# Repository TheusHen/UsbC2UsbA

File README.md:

# USB-C to USB-A Adapter
My first PCB, warming up and learning to Hack Club Highway 2026!

## PCB:

*Layers: 2*

*Dimensions: 30.6 x 63.2 mm*

### License: [GPLv3](https://www.gnu.org/licenses/gpl-3.0.html)

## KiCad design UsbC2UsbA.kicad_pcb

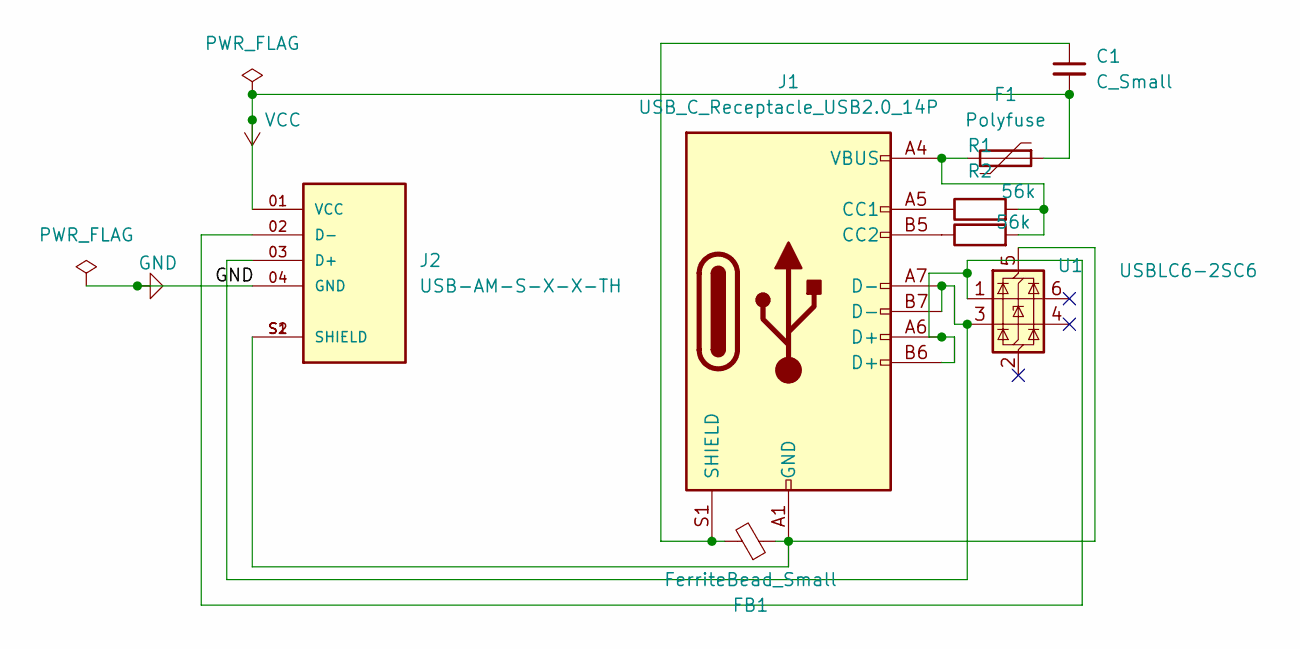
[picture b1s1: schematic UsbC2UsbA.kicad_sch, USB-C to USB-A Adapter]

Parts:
C1: C_Small; C_0603_1608Metric
F1: Polyfuse; Fuse_Schurter_UMT250
FB1: FerriteBead_Small; LairdTech_28C0236-0JW-10
J1: USB_C_Receptacle_USB2.0_14P; USB_C_Receptacle_HRO_TYPE-C-31-M-12
J2: USB-AM-S-X-X-TH; SAMTEC_USB-AM-S-X-X-TH; PARTREV U
R1, R2: 56k; R_0603_1608Metric
U1: USBLC6-2SC6; SOT-23-6

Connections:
GND: J2.04 (GND)
unnamed: F1.2, J1.A4 (VBUS), J1.A9 (VBUS), J1.B4 (VBUS), J1.B9 (VBUS), R1.2, R2.2
unnamed: J1.A5 (CC1), R1.1
unnamed: J1.B5 (CC2), R2.1
unnamed: C1.1, FB1.2, J1.S1 (SHIELD)
unnamed: J1.A7 (D-), J1.B7 (D-), J2.03 (D+), U1.3 (I/O2)
unnamed: J1.A6 (D+), J1.B6 (D+), J2.02 (D-), U1.1 (I/O1)
unnamed: FB1.1, J1.A1 (GND), J1.A12 (GND), J1.B1 (GND), J1.B12 (GND), J2.S1 (SHIELD), J2.S2 (SHIELD), U1.5 (VBUS)
VCC: C1.2, F1.1, J2.01 (VCC)

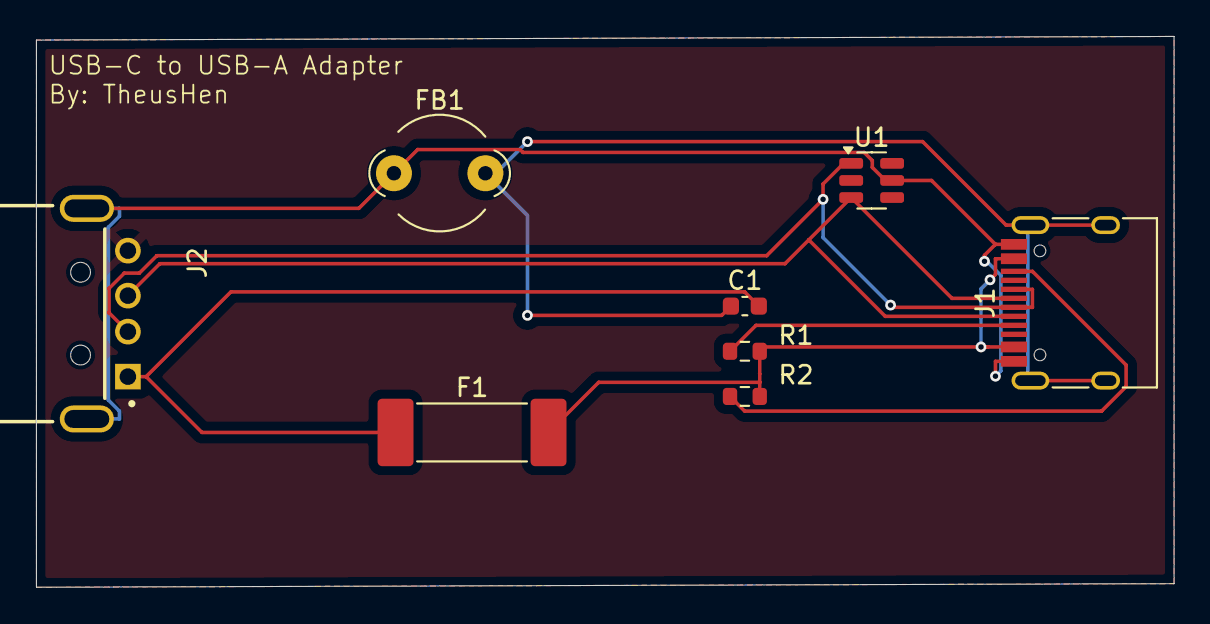
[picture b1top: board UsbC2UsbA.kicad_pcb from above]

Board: 2 copper layers, 63.2 x 30.6 mm, 8 parts (0 on the bottom side), 8 nets.

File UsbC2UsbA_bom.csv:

"Id";"Designador";"Footprint";"Quantidade";"Designação";"Fornecedor e referência";
1;"J2";"SAMTEC_USB-AM-S-X-X-TH";1;"USB-AM-S-X-X-TH";;;
2;"FB1";"LairdTech_28C0236-0JW-10";1;"FerriteBead_Small";;;
3;"F1";"Fuse_Schurter_UMT250";1;"Polyfuse";;;
4;"R1,R2";"R_0603_1608Metric";2;"56k";;;
5;"J1";"USB_C_Receptacle_HRO_TYPE-C-31-M-12";1;"USB_C_Receptacle_USB2.0_14P";;;
6;"U1";"SOT-23-6";1;"USBLC6-2SC6";;;
7;"C1";"C_0603_1608Metric";1;"C_Small";;;

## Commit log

2025-08-04 Saving PCB Files
2025-08-04 Fixed CSV
2025-08-04 Created CONTRIBUTING.md
2025-08-04 CONTRIBUTING.md -> ./github
2025-08-04 Created LEARN.md
